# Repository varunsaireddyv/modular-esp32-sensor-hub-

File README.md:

# modular-esp32-sensor-hub-
Introduction:

This project is a modular ESP32-based sensor hub designed for rapid prototyping and monitoring environements. It supports a wide range of sensors through hot-swappable connectors, with onboard SD card logging, and runs off a 5v li-ion battery. The goal is to offer a deployable, plug-and-play embedded system that’s both scalable and user-friendly.

Primary Design Goals:

Modularity:hot-swappable sensor ports for analog, digital, and I2C devices, swapable power source, programable ESP board

Deployability:standalone and swapable power and onboard storage, light weight custom ESP 32 WROOM 32D board

Plug-and-play:Firmware pre installed and no user input required exept for conecting sensors to premaped sensor pins

---

## Features

- ESP32-WROOM-32D core (Wi-Fi + BLE)
- 13 modular sensor ports: digital, analog, and I2C
- MicroSD card support (SPI) for data logging
- 0.96" OLED screen support via I2C
- Shared I2C bus (GPIO21/GPIO22) with pull-up planning
- Dual voltage rails: 5V (VBUS) and 3.3V (via AMS1117 regulator)
- USB or Li-ion battery input with diode-based auto-switching
- Ground stitched bottom layer with dedicated signal routing on top
- Wide traces (1mm) for power, separate analog and digital zones
- Modular firmware (coming soon)

---

## Pin Mapping

| Function            | GPIO Pin   |
|---------------------|------------|
| I2C SDA             | GPIO21     |
| I2C SCL             | GPIO22     |
| SD Card CS          | GPIO5      |
| SD Card CLK         | GPIO18     |
| SD Card MOSI        | GPIO23     |
| SD Card MISO        | GPIO19     |
| Analog Sensor 1     | GPIO32     |
| Analog Sensor 2     | GPIO33     |
| Digital Sensor 1    | GPIO25     |
| Digital Sensor 2    | GPIO26     |
| Digital Sensor 3    | GPIO27     |
| Digital Sensor 4    | GPIO14     |
| Digital Sensor 5    | GPIO12     |
| Digital Sensor 6    | GPIO13     |
| OLED (I2C)          | Shared     |
| I2C Misc Ports 1-2  | Shared     |

> All analog lines use 1k/2k voltage dividers to drop from 5V to 3.3V safe levels for the ESP32. All sensors are routed through XH-3P connectors with GND, VCC, and Signal/I2C.

---

## Supported Sensors(Default in Firmware)

### Analog / Digital Sensors
- MQ135 (Air Quality)
- DHT22 (Temp & Humidity)
- Raindrop Sensor
- Sound Sensor (x2)
- Soil Moisture
- LDR (Light)
- IR Receiver

### I2C Sensors & Modules
- MPU6050 (Accel + Gyro)
- BME280 (Temp + Pressure + Humidity)
- BH1750 (Light)
- OLED Display

---

## Included Files/Folders

- Schematic: `ESP32_WROOM_D.kicad_sch`
- Board Layout: `PCB_main.kicad_pcb`
- Schematic PNG preview: `Schemtaic.png`
- 3D render: `PCB.png`
- 3D render front: `PCB_F.png`
- 3D render back: `PCB_B.png`
- License: MIT
- Firmware: src/, include/,  lib/, "platform.ini"
- Documents: "ERC", "DRC", "Datasheet", "Pin_mapping"

---

## Firmware flow

main.cpp :
-Calls SensorManager.begin() → initializes I2C, sets up pins
-Calls SensorManager.detectConnectedSensors() → auto-detects attached sensors
-Calls SensorManager.readAll() repeatedly inside loop() to read & print sensor data

sensormanger.cpp/.h :
-Defines bool flags for each supported sensor
-Each sensor has its own analogRead() or I2C detection logic
-readAll() only reads sensors that were marked as detected(bool=true)

pins.h :
-Central place to edit pin numbers (for future boards or remapping)
-Also includes notes on analog/digital/I2C mappings

---

## Adding own sensors

You can plug in any new sensor to unused analog/digital/I2C ports. Here’s how to support it in firmware:

Step 1 : Wiring :

-Connect the sensor to a free port (check Pin Mapping table)
-Use correct GND/VCC/SIG (XH-3P)

step 2 : Modify "sensormanger.h" :
   
  -Add a flag for presence detection :
      
    extern bool NEW_SENSOR_present;

step 3 : Modify "pins.h" :
   
  -define your sensor with its GIO pin :
  
    #define NEW_SENSOR_PIN ##   //replace ## with GIO pin(can be found in sensor data sheet)

step 4 : Modify "sensormanger.cpp" :

  -In detectConnectedSensors add :
  
    -if (analogRead(NEW_SENSOR_PIN) > 50) NEW_SENSOR_present = true;   //(for analog sensors)
    -if (analogRead(NEW_SENSOR_PIN) > 50) NEW_SENSOR_present = true;   //(for digital sensors)
    -Check sensor library for I2C (differs from sensor to sensor reffer sesnormanager.cpp for refrence)
   
  -In readAll add :
  
    -if (NEW_SENSOR_present) {
      int val = analogRead(NEW_SENSOR_PIN);   //(for analog)
      }
    -if (NEW_SENSOR_present) {
      int val = digitalRead(NEW_SENSOR_PIN);   //(for analog)
        }
      -Check sensor library for I2C (differs from sensor to sensor reffer sesnormanager.cpp for refrence)

step 5 : SD card logging 

-5.1 : Update sdlogger.h : 

  -In sdlogger.h, go to the writeRow() function declaration. Add your new sensor’s argument at the end:
  
    void writeRow(
        String timestamp,
        ...
        String BH1750,
        String NEW_SENSOR      //<-- Add this
    ) ;

5.2 : Update sdlogger.cpp :

  -Update the writeRow() definition:
  -Add the new parameter to the function like:
  
    void writeRow(
        String timestamp,
        ...
        String BH1750,
        String NEW_SENSOR       //<-- Add here too
    ) {
  -Add it to the file write block:
  -Scroll to where values are written into the file. Append this:

    file.print(NEW_SENSOR); file.println();    //<-- Just before file.close();
  -Update the CSV header:
  -Only needed once, in the same file (inside if (!SD.exists("/logs.csv"))):

    file.println("Time stamp,MQ135-D,MQ135-A,DHT22,RAIN-A,RAIN-D,SOUND-A,SOUND-D,SOIL-A,SOIL-D,MPU6050,BMP180,BH1750,NEW_SENSOR");

5.3 : Modify readAll() in SensorManager :
  -If your sensor is optional/detectable:

    String newSensorValue = "NA";
    if (NEW_SENSOR_present) {
      int val = analogRead(NEW_SENSOR_PIN);  // or digitalRead / I2C
      newSensorValue = String(val);

  -Then pass it to the logger:

    SdLogger::writeRow(
      timestamp,
      mq135_d, mq135_a,
      dht22,
      rain_a, rain_d,
      sound_a, sound_d,
      soil_a, soil_d,
      mpu6050,
      bmp180,
      bh1750,
      newSensorValue       //<-- Final argument
    );
    }

---

## Flashing the Board (PlatformIO)

To upload firmware to the ESP32 board:

1. Install PlatformIO:

   -VSCode + PlatformIO extension
   -Or via CLI: https://platformio.org/install/cli
   
3. Clone this repo:
   
    -git clone https://github.com/varunsaireddyv/modular-esp32-sensor-hub-.git
    -cd modular-esp32-sensor-hub-
   
5. Plug in the board via USB
   
6. Build and upload
    -pio run --target upload

---

## Hardware Design Notes

- 2-layer PCB: Top for signals, Bottom for full GND plane
- GND stitching via multiple vias across zones
- AMS1117 regulator outputs 3.3V rail, with thick trace routing
- Diode-logic used to auto-select between USB or battery power
- All connectors: XH-3P format for modularity
- I2C pull-up resistors placed close to MCU

---

## License

This project is licensed under the MIT License. See `LICENSE` file for full terms.
You may freely modify, distribute, or use this project in your own designs.

## For hire !!
reach out at : varunbillas@gmail.com

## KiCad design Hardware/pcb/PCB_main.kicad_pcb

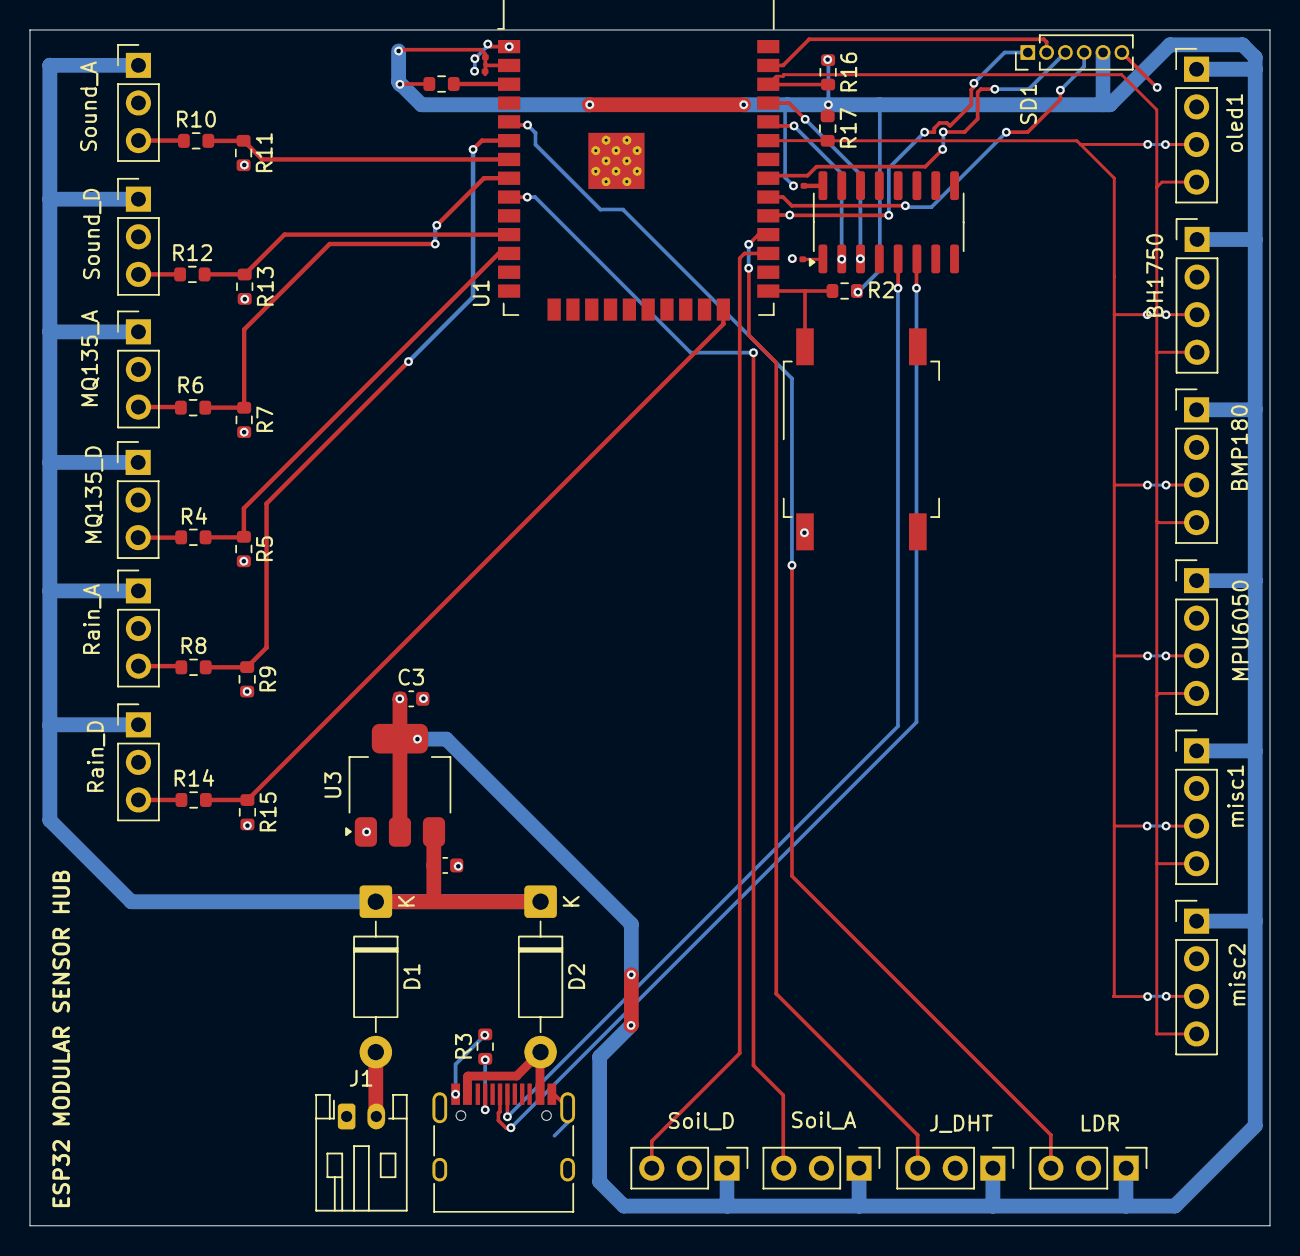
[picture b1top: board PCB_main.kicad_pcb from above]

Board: 2 copper layers, 83.8 x 80.8 mm, 48 parts (0 on the bottom side), 36 nets.

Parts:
BH1750: Conn_01x04; PinHeader_1x04_P2.54mm_Vertical
BMP180: Conn_01x04; PinHeader_1x04_P2.54mm_Vertical
C1: 10uF; C_0201_0603Metric
C2: 0.1uF; C_0201_0603Metric
C3: 22uF; C_0603_1608Metric
C4: 10uF; C_0603_1608Metric
C5, C6: 100nF; C_0201_0603Metric
D1, D2: 1N5819; D_DO-41_SOD81_P10.16mm_Horizontal
J1: Conn_01x02; JST_PH_S2B-PH-K_1x02_P2.00mm_Horizontal
J_DHT: Conn_01x03; PinHeader_1x03_P2.54mm_Vertical
LDR: Conn_01x03; PinHeader_1x03_P2.54mm_Vertical
MPU6050: Conn_01x04; PinHeader_1x04_P2.54mm_Vertical
MQ135_A, MQ135_D: Conn_01x03; PinHeader_1x03_P2.54mm_Vertical
P1: USB_C_Plug_USB2.0; USB_C_Receptacle_HRO_TYPE-C-31-M-12
R1, R2, R4, R6, R8, R10, R12, R14: 10kΩ; R_0603_1608Metric
R3: 5.1kΩ; R_0603_1608Metric
R5, R7, R9, R11, R13, R15: 6.2kΩ; R_0603_1608Metric
R16, R17: 4.7kΩ; R_0603_1608Metric
Rain_A: Conn_01x03; PinHeader_1x03_P2.54mm_Vertical
Rain_D: Conn_01x03; PinHeader_1x03_P2.54mm_Vertical
SD1: Conn_01x06; PinHeader_1x06_P1.27mm_Vertical
SW1: BOOT OPTION; SW_MEC_5GSH9
Soil_A: Conn_01x03; PinHeader_1x03_P2.54mm_Vertical
Soil_D: Conn_01x03; PinHeader_1x03_P2.54mm_Vertical
Sound_A: Conn_01x03; PinHeader_1x03_P2.54mm_Vertical
Sound_D: Conn_01x03; PinHeader_1x03_P2.54mm_Vertical
U1: exp32wroomd; ESP32-WROOM-32D
U2: CH340C; SOIC-16_3.9x9.9mm_P1.27mm
U3: AMS1117-3.3; SOT-223-3_TabPin2
misc1, misc2: Conn_01x04; PinHeader_1x04_P2.54mm_Vertical
oled1: Conn_01x04; PinHeader_1x04_P2.54mm_Vertical

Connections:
+3.3V: BH1750.1, BMP180.1, C1.1, C2.1, C3.1, C5.2, J_DHT.1, LDR.1, MPU6050.1, R1.1, R2.2, R16.1, R17.1, SD1.5, Soil_A.1, Soil_D.1, U1.2 (3V3), U3.2 (VO), misc1.1, misc2.1, oled1.1
/5v(r): C4.1, D1.1 (K), D2.1 (K), MQ135_A.1, MQ135_D.1, Rain_A.1, Rain_D.1, Sound_A.1, Sound_D.1, U3.3 (VI)
D+: P1.A6 (D+), U2.6 (UD-)
D-: P1.A7 (D-), U2.5 (UD+)
GND: BH1750.2, BMP180.2, C1.2, C2.2, C3.2, C4.2, C6.1, J1.1, J_DHT.2, LDR.2, MPU6050.2, MQ135_A.2, MQ135_D.2, P1.A1 (GND), P1.A12 (GND), P1.B1 (GND), P1.B12 (GND), P1.S1 (SHIELD), R3.2, R5.2, R7.2, R9.2, R11.2, R13.2, R15.2, Rain_A.2, Rain_D.2, SD1.6, SW1.2, Soil_A.2, Soil_D.2, Sound_A.2, Sound_D.2, U1.1 (GND), U3.1 (GND), misc1.2, misc2.2, oled1.2
IO2: R14.1, Rain_D.3
IO5: SD1.1, U1.29 (GPIO5)
IO16: Soil_D.3, U1.27 (GPIO16)
IO17: J_DHT.3, U1.28 (GPIO17)
IO18: SD1.4, U1.30 (GPIO18)
IO19: SD1.3, U1.31 (GPIO19)
IO26: R12.1, Sound_D.3
IO27: MQ135_D.3, R4.1
IO32: MQ135_A.3, R6.1
IO33: Soil_A.3, U1.9 (GPIO33)
IO34: R8.1, Rain_A.3
IO35: R10.1, Sound_A.3
IO39: LDR.3, U1.5 (GPIO39)
IO123: SD1.2, U1.37 (GPIO23)
unnamed: D1.2 (A), J1.2
unnamed: P1.A5 (CC), R3.1
unnamed: R1.2, U1.3 (EN)
unnamed: R2.1, SW1.1, U1.25 (GPIO0)
unnamed: R14.2, R15.1, U1.24 (GPIO2)
unnamed: R12.2, R13.1, U1.11 (GPIO26)
unnamed: R4.2, R5.1, U1.12 (GPIO27)
unnamed: R6.2, R7.1, U1.8 (GPIO32)
unnamed: R8.2, R9.1, U1.6 (GPIO34)
unnamed: R10.2, R11.1, U1.7 (GPIO35)
unnamed: C6.2, U2.1 (GND)
unnamed: C5.1, U2.16 (VCC)
RX0: U1.35 (GPIO1), U2.3 (RXD)
SCL: BH1750.3, BMP180.3, MPU6050.3, R17.2, U1.33 (GPIO21), misc1.3, misc2.3, oled1.3
SDA: BH1750.4, BMP180.4, MPU6050.4, R16.2, U1.36 (GPIO22), misc1.4, misc2.4, oled1.4
TX0: U1.34 (GPIO3), U2.2 (TXD)
VBUS(5v): D2.2 (A), P1.A4 (VBUS), P1.A9 (VBUS), P1.B4 (VBUS), P1.B9 (VBUS)

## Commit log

2025-06-15 Add placeholder files to track empty directories
2025-06-16 Updated schematic
2025-06-17 PCB base
2025-06-18 PCB Final
2025-06-19 Create LICENSE
2025-06-20 Base firmware
2025-06-21 Firmware penultimate
2025-06-22 src completed
